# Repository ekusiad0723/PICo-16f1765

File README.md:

# PICo-16f1765
ブレッドボードで使えるPIC16f1765の開発基板だよ

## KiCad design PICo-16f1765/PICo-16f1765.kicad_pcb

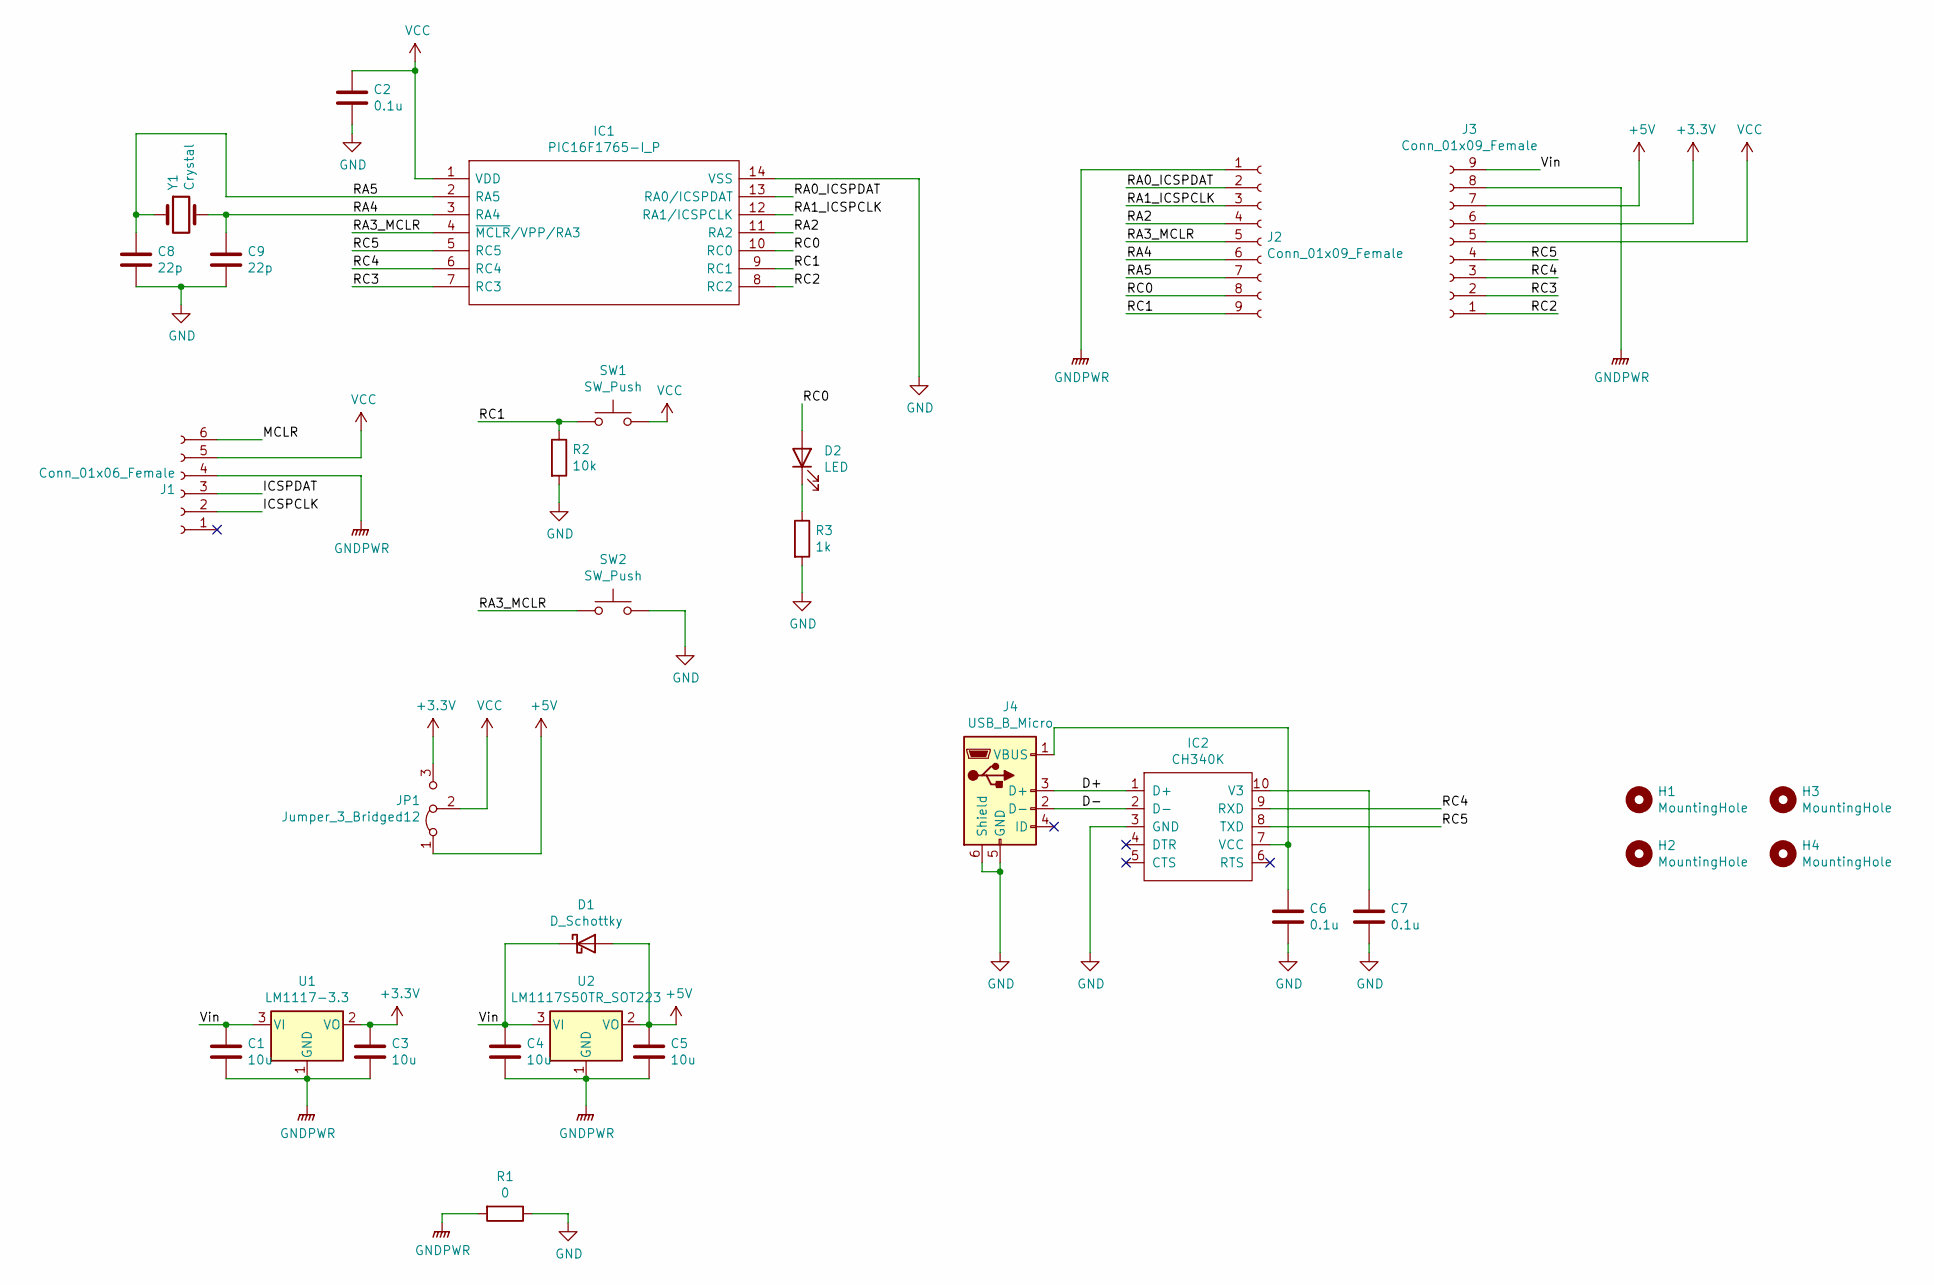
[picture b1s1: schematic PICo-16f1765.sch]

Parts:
C1, C3, C4, C5: 10u; C_0603_1608Metric
C2, C6, C7: 0.1u; C_0603_1608Metric
C8, C9: 22p; C_0603_1608Metric
D1: D_Schottky; D_1206_3216Metric
D2: LED; LED_0603_1608Metric
H1, H2, H3, H4: MountingHole; MountingHole_2.2mm_M2
IC1: PIC16F1765-I_P; DIP-14_W7.62mm_Socket
IC2: CH340K; SSOP-10_3.9x4.9mm_P1.00mm
J1: Conn_01x06_Female; PinHeader_1x06_P2.54mm_Horizontal
J2, J3: Conn_01x09_Female; PinHeader_1x09_P2.54mm_Vertical
J4: USB_B_Micro; ZX62B5PA33
JP1: Jumper_3_Bridged12; SolderJumper-3_P1.3mm_Bridged2Bar12_RoundedPad1.0x1.5mm
R1: 0; R_0603_1608Metric
R2: 10k; R_0603_1608Metric
R3: 1k; R_0603_1608Metric
SW1, SW2: SW_Push; TVAF06A020BR
U1: LM1117-3.3; SOT-223-3_TabPin2
U2: LM1117S50TR_SOT223; SOT-223-3_TabPin2
Y1: Crystal; Crystal_HC49-U_Vertical

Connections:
+3V3: C3.1, J3.6, JP1.3 (B), U1.2 (VO)
+5V: C5.1, D1.2 (A), J3.7, JP1.1 (A), U2.2 (VO)
/D+: IC2.1 (D+), J4.3 (D+)
/D-: IC2.2 (D-), J4.2 (D-)
/ICSPCLK: J1.2
/ICSPDAT: J1.3
/MCLR: J1.6
/RA0_ICSPDAT: IC1.13 (RA0/ICSPDAT), J2.2
/RA1_ICSPCLK: IC1.12 (RA1/ICSPCLK), J2.3
/RA2: IC1.11 (RA2), J2.4
/RA3_MCLR: IC1.4 (~MCLR~/VPP/RA3), J2.5, SW2.1
/RA4: C9.1, IC1.3 (RA4), J2.6, Y1.2
/RA5: C8.1, IC1.2 (RA5), J2.7, Y1.1
/RC0: D2.2 (A), IC1.10 (RC0), J2.8
/RC1: IC1.9 (RC1), J2.9, R2.1, SW1.1
/RC2: IC1.8 (RC2), J3.1
/RC3: IC1.7 (RC3), J3.2
/RC4: IC1.6 (RC4), IC2.9 (RXD), J3.3
/RC5: IC1.5 (RC5), IC2.8 (TXD), J3.4
/Vin: C1.1, C4.1, D1.1 (K), J3.9, U1.3 (VI), U2.3 (VI)
GND: C2.2, C6.2, C7.2, C8.2, C9.2, IC1.14 (VSS), IC2.3 (GND), J4.5 (GND), J4.6 (Shield), R1.1, R2.2, R3.2, SW2.2
GNDPWR: C1.2, C3.2, C4.2, C5.2, J1.4, J2.1, J3.8, R1.2, U1.1 (GND), U2.1 (GND)
unnamed: C6.1, IC2.7 (VCC), J4.1 (VBUS)
unnamed: C7.1, IC2.10 (V3)
unnamed: D2.1 (K), R3.1
VCC: C2.1, IC1.1 (VDD), J1.5, J3.5, JP1.2 (C), SW1.2

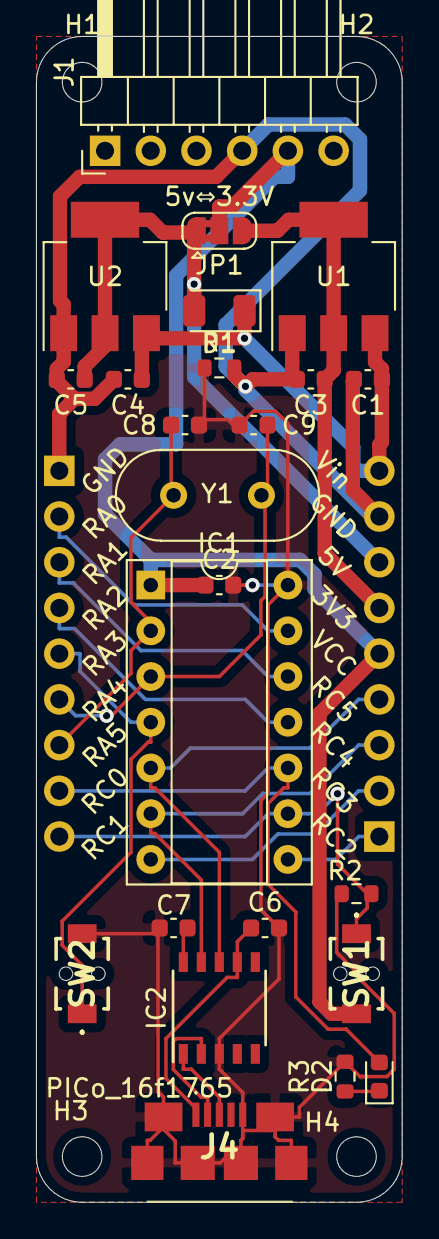
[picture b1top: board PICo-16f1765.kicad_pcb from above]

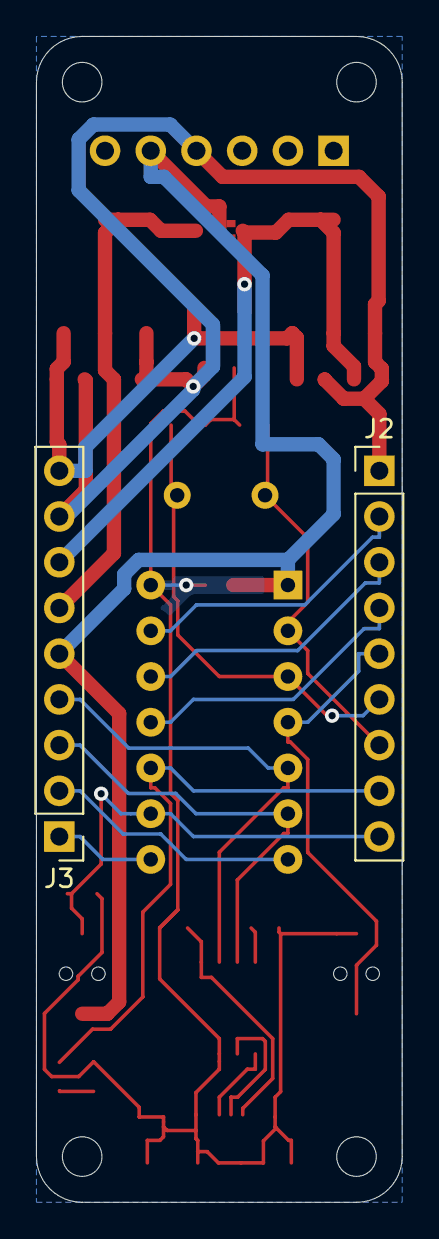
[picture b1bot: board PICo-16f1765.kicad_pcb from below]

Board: 2 copper layers, 20.3 x 64.8 mm, 30 parts (2 on the bottom side), 23 nets.

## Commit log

2023-05-20 add: schematic
2023-05-20 add: library files
2023-06-12 feat: shape
2023-06-13 kansei
2023-06-13 add: gerber
2023-06-13 update: files
2023-06-13 fix: silks
2024-12-16 add: someconnector
